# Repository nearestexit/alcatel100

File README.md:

# alcatel100

Custom keyboard designed to use the GMK keycaps from the [Alcatel-Lucent MMK](https://deskthority.net/viewtopic.php?t=23887).
Designed in Onshape and KiCad.
Powered by [QMK](https://github.com/qmk/qmk_firmware).

## Overview
The Alcatel MMK has a beautiful set of keycaps, but the Enter, Backspace, and Right Shift are 0.25u shorter than normal. They are rarely, if ever, used on customs.
The keycaps were originally made by Cherry, but later GMK took over production.

I designed this for fun. It is not an entry-level keyboard, and it is not intended for a Group Buy.
I'm sharing the production and source files with the goal of serving as a reference for other designers.

## Design Goals
- Box-on-wedge with seamless sides all around, including the back
- Left half of the keyboard isolated from the right half
- Single-color PWM-dimmable backlight
- Uniform 4.8mm bezels

**Case Source (Onshape):** https://cad.onshape.com/documents/5081b96c77523c56bb0f8f6b/w/91dc47074a8fd3b0ca2e25d0/e/6e8ed4262c52380f9f8bfe9b

## PCB
The PCB supports both configurations of split right shift, and also split numpad enter. Unfortunately, after the PCB was manufactured, I discovered that the Cherry version of the keyset has a 6.25u spacebar that only has an offset stem, while the GMK version of the keyset has a 6.25u spacebar that supports both centered and offset stems. The PCB and bottom case only support the centered stem location.
I ordered a single bare PCB from EuroCircuits and hand-soldered the components, so I do not have JLCPCB production files available.

## Bill of Materials

| Item  | Quantity | Link |
| ------------- | ------------- | ------------- | 
| Ribbon Cable | 1 | https://www.digikey.com/en/products/detail/molex/0151660207/3281088 |
| 3M SJ5302 | 4  | https://www.3m.com/3M/en_US/p/d/b5005035183/ |
| Unified Daughterboard  | 1  | https://cannonkeys.com/products/unified-daughterboard-and-jst-cable |
| M2.5x0.45x8mm SHCS | 6  | https://www.mcmaster.com/91292A012/ |
| 10cm Molex to JST Cable | 1 | https://cannonkeys.com/products/unified-daughterboard-and-jst-cable |
| M2.5x0.45x16mm SHCS | 1 | https://www.mcmaster.com/91292A018/ |
| M2.5x0.45x20mm SHCS | 6 | https://www.mcmaster.com/91292A019/ |
| M2x0.4x4mm SHCS | 10 | https://www.mcmaster.com/91292A005/ |
| M3x0.5x6mm Countersunk Screw | 5 | https://www.mcmaster.com/92125A126/ |
| M3x0.5x8mm Countersunk Screw | 8 | https://www.mcmaster.com/92125A128/ |

## Backlight

Each lock light is controlled by a separate pin and has a fixed brightness. The remainder of the windowed keys are all on the same PWM dimmable circuit.
I used [these LEDs](https://www.digikey.com/en/products/detail/american-bright-optoelectronics-corporation/BL-B8141-TRS20A/22486924), which have a nice color, but MX LEDs are actually supposed to be 3mm *flangeless* LEDs. These LEDs are *flanged* 3mm. I had to clip off all the flanges (not fun).

## Firmware

A QMK .bin file is provided for flashing, as well as QMK source files. I can port it to Vial upon request.

## Credits

Everyone in the Keyboard Atelier who has helped me over the past 2 years.

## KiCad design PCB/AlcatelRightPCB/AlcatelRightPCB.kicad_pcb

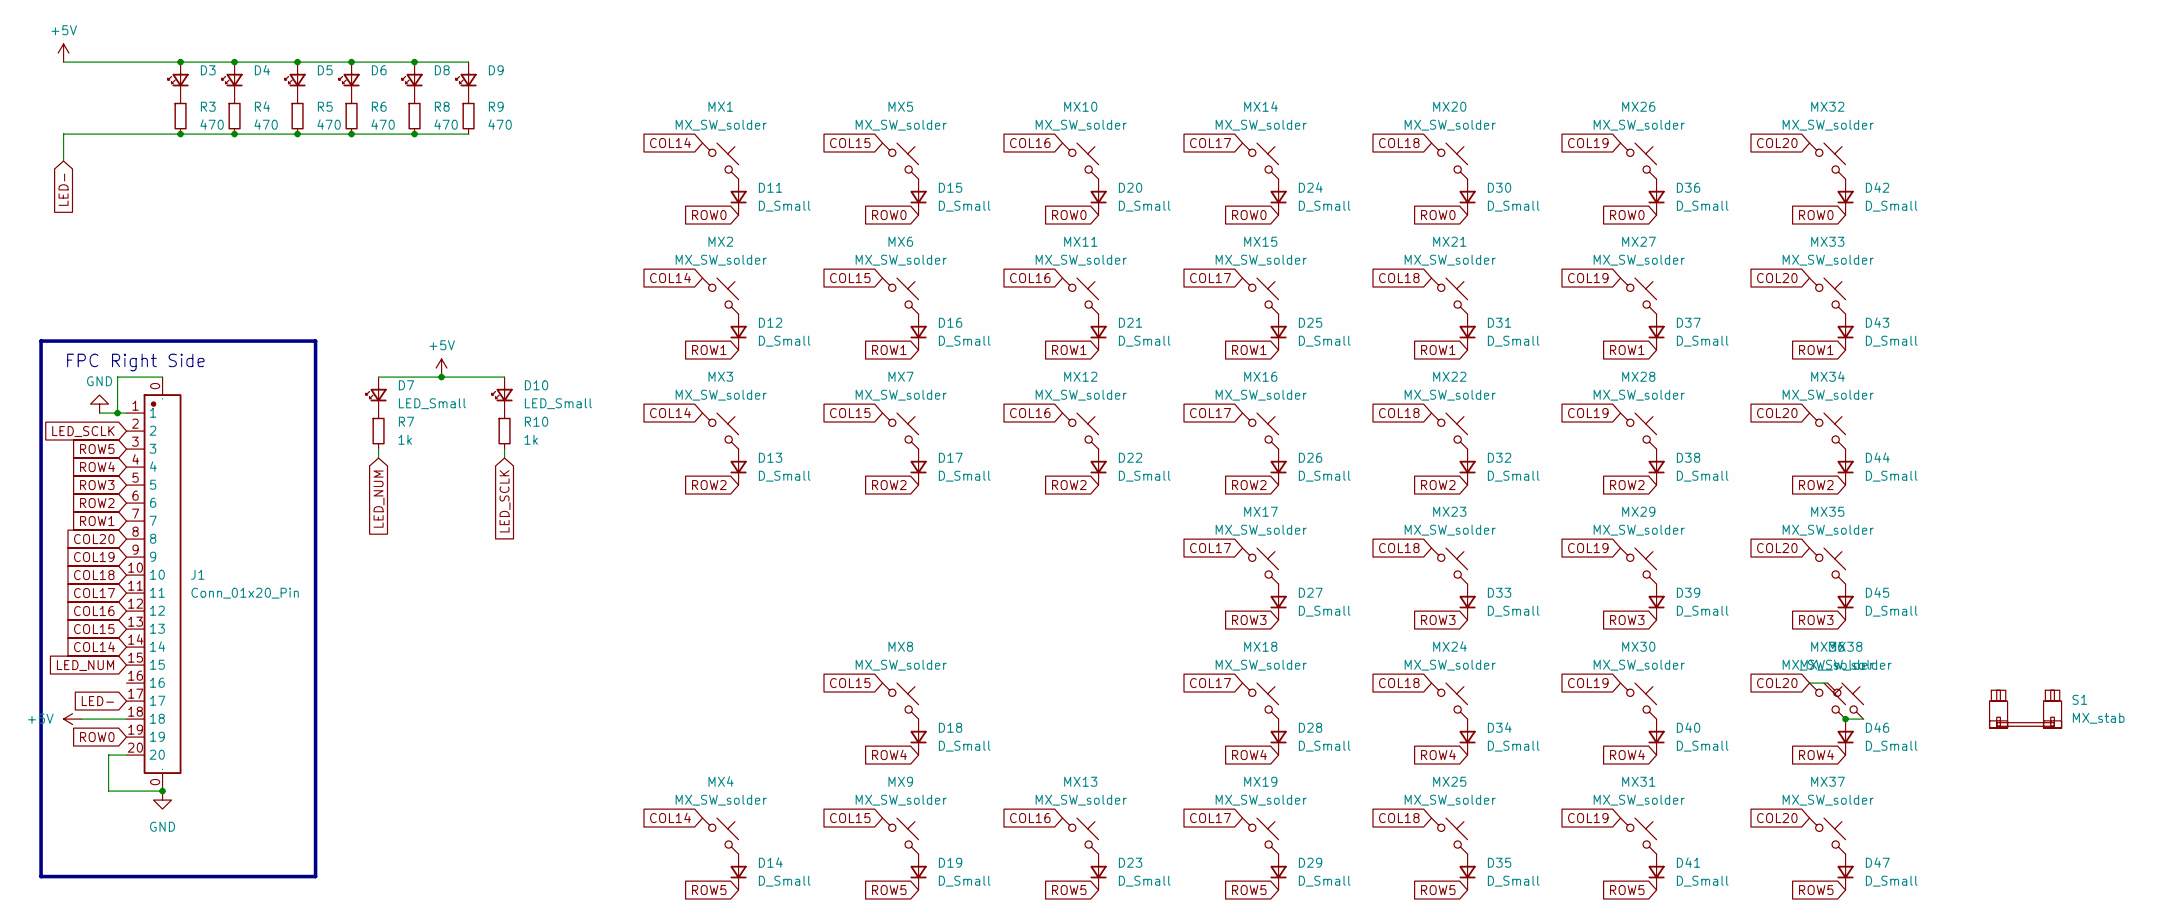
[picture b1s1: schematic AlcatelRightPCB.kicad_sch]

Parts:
D3, D4, D5, D6, D8, D9: LED_MX_3mm_Offset
D7, D10: LED_Small; LED_MX_3mm_Offset
D11, D12, D13, D14, D15, D16, D17, D18, D19, D20, D21, D22, D23, D24, D25, D26, D27, D28, D29, D30, D31, D32, D33, D34, D35, D36, D37, D38, D39, D40, D41, D42, D43, D44, D45, D46, D47: D_Small; D_SOD-123_ShiftedSilkscreen
J1: Conn_01x20_Pin; CONN-SMD_20P-P0.50_10051922-2010ELF
MX1, MX2, MX3, MX4, MX5, MX6, MX7, MX8, MX9, MX10, MX11, MX12, MX13, MX14, MX15, MX16, MX17, MX18, MX19, MX20, MX21, MX22, MX23, MX24, MX25, MX26, MX27, MX28, MX29, MX30, MX31, MX32, MX33, MX34, MX35, MX36, MX37: MX_SW_solder; SW_MX_1u
MX38: MX_SW_solder; SW_MX_HS_CPG151101S11_No_PTH_Edge
R3, R4, R5, R6, R8, R9: 470; R_0805_2012Metric
R7, R10: 1k; R_0805_2012Metric
S1: MX_stab; STAB_MX_2u

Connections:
+5V: D3.2 (A), D4.2 (A), D5.2 (A), D6.2 (A), D7.2 (A), D8.2 (A), D9.2 (A), D10.2 (A), J1.18
COL14: J1.14, MX1.1, MX2.1, MX3.1, MX4.1
COL15: J1.13, MX5.1, MX6.1, MX7.1, MX8.1, MX9.1
COL16: J1.12, MX10.1, MX11.1, MX12.1, MX13.1
COL17: J1.11, MX14.1, MX15.1, MX16.1, MX17.1, MX18.1, MX19.1
COL18: J1.10, MX20.1, MX21.1, MX22.1, MX23.1, MX24.1, MX25.1
COL19: J1.9, MX26.1, MX27.1, MX28.1, MX29.1, MX30.1, MX31.1
COL20: J1.8, MX32.1, MX33.1, MX34.1, MX35.1, MX36.1, MX37.1, MX38.1
GND: J1.0, J1.1, J1.20
LED-: J1.17, R3.2, R4.2, R5.2, R6.2, R8.2, R9.2
LED_NUM: J1.15, R7.2
LED_SCLK: J1.2, R10.2
unnamed: D3.1 (K), R3.1
unnamed: D4.1 (K), R4.1
unnamed: D5.1 (K), R5.1
unnamed: D6.1 (K), R6.1
unnamed: D7.1 (K), R7.1
unnamed: D8.1 (K), R8.1
unnamed: D9.1 (K), R9.1
unnamed: D10.1 (K), R10.1
unnamed: D11.2 (A), MX1.2
unnamed: D12.2 (A), MX2.2
unnamed: D13.2 (A), MX3.2
unnamed: D14.2 (A), MX4.2
unnamed: D15.2 (A), MX5.2
unnamed: D16.2 (A), MX6.2
unnamed: D17.2 (A), MX7.2
unnamed: D18.2 (A), MX8.2
unnamed: D19.2 (A), MX9.2
unnamed: D20.2 (A), MX10.2
unnamed: D21.2 (A), MX11.2
unnamed: D22.2 (A), MX12.2
unnamed: D23.2 (A), MX13.2
unnamed: D24.2 (A), MX14.2
unnamed: D25.2 (A), MX15.2
unnamed: D26.2 (A), MX16.2
unnamed: D27.2 (A), MX17.2
unnamed: D28.2 (A), MX18.2
unnamed: D29.2 (A), MX19.2
unnamed: D30.2 (A), MX20.2
unnamed: D31.2 (A), MX21.2
unnamed: D32.2 (A), MX22.2
unnamed: D33.2 (A), MX23.2
unnamed: D34.2 (A), MX24.2
unnamed: D35.2 (A), MX25.2
unnamed: D36.2 (A), MX26.2
unnamed: D37.2 (A), MX27.2
unnamed: D38.2 (A), MX28.2
unnamed: D39.2 (A), MX29.2
unnamed: D40.2 (A), MX30.2
unnamed: D41.2 (A), MX31.2
unnamed: D42.2 (A), MX32.2
unnamed: D43.2 (A), MX33.2
unnamed: D44.2 (A), MX34.2
unnamed: D45.2 (A), MX35.2
unnamed: D46.2 (A), MX36.2, MX38.2
unnamed: D47.2 (A), MX37.2
ROW0: D11.1 (K), D15.1 (K), D20.1 (K), D24.1 (K), D30.1 (K), D36.1 (K), D42.1 (K), J1.19
ROW1: D12.1 (K), D16.1 (K), D21.1 (K), D25.1 (K), D31.1 (K), D37.1 (K), D43.1 (K), J1.7
ROW2: D13.1 (K), D17.1 (K), D22.1 (K), D26.1 (K), D32.1 (K), D38.1 (K), D44.1 (K), J1.6
ROW3: D27.1 (K), D33.1 (K), D39.1 (K), D45.1 (K), J1.5
ROW4: D18.1 (K), D28.1 (K), D34.1 (K), D40.1 (K), D46.1 (K), J1.4
ROW5: D14.1 (K), D19.1 (K), D23.1 (K), D29.1 (K), D35.1 (K), D41.1 (K), D47.1 (K), J1.3

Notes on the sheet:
FPC Right Side

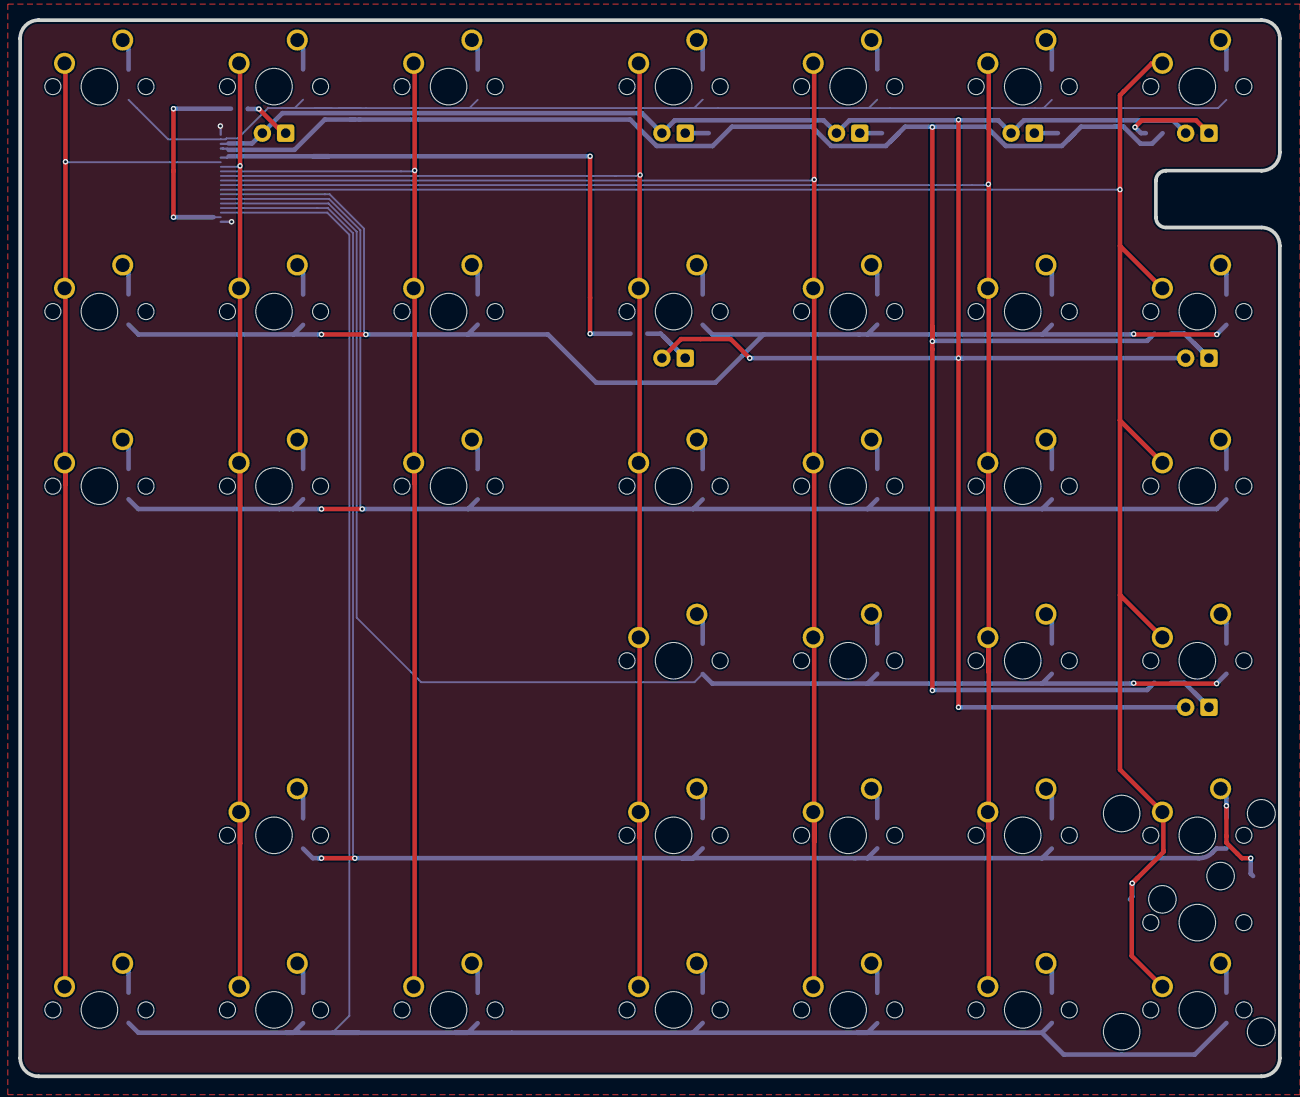
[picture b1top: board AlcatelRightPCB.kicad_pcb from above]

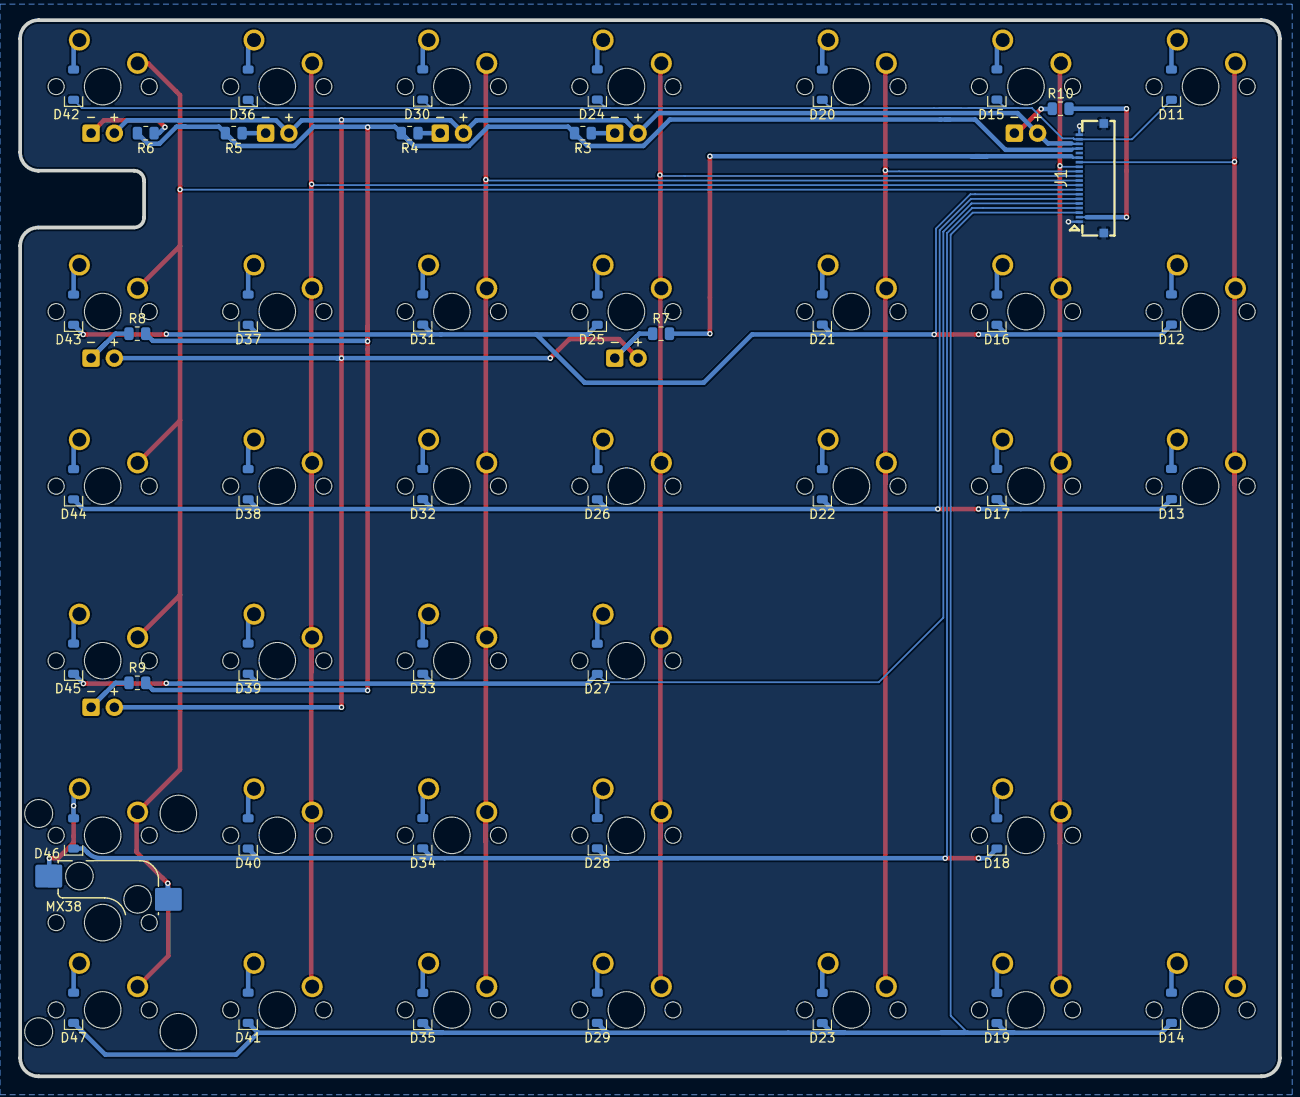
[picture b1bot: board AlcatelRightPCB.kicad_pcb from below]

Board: 2 copper layers, 137.5 x 115.2 mm, 93 parts (47 on the bottom side), 63 nets.

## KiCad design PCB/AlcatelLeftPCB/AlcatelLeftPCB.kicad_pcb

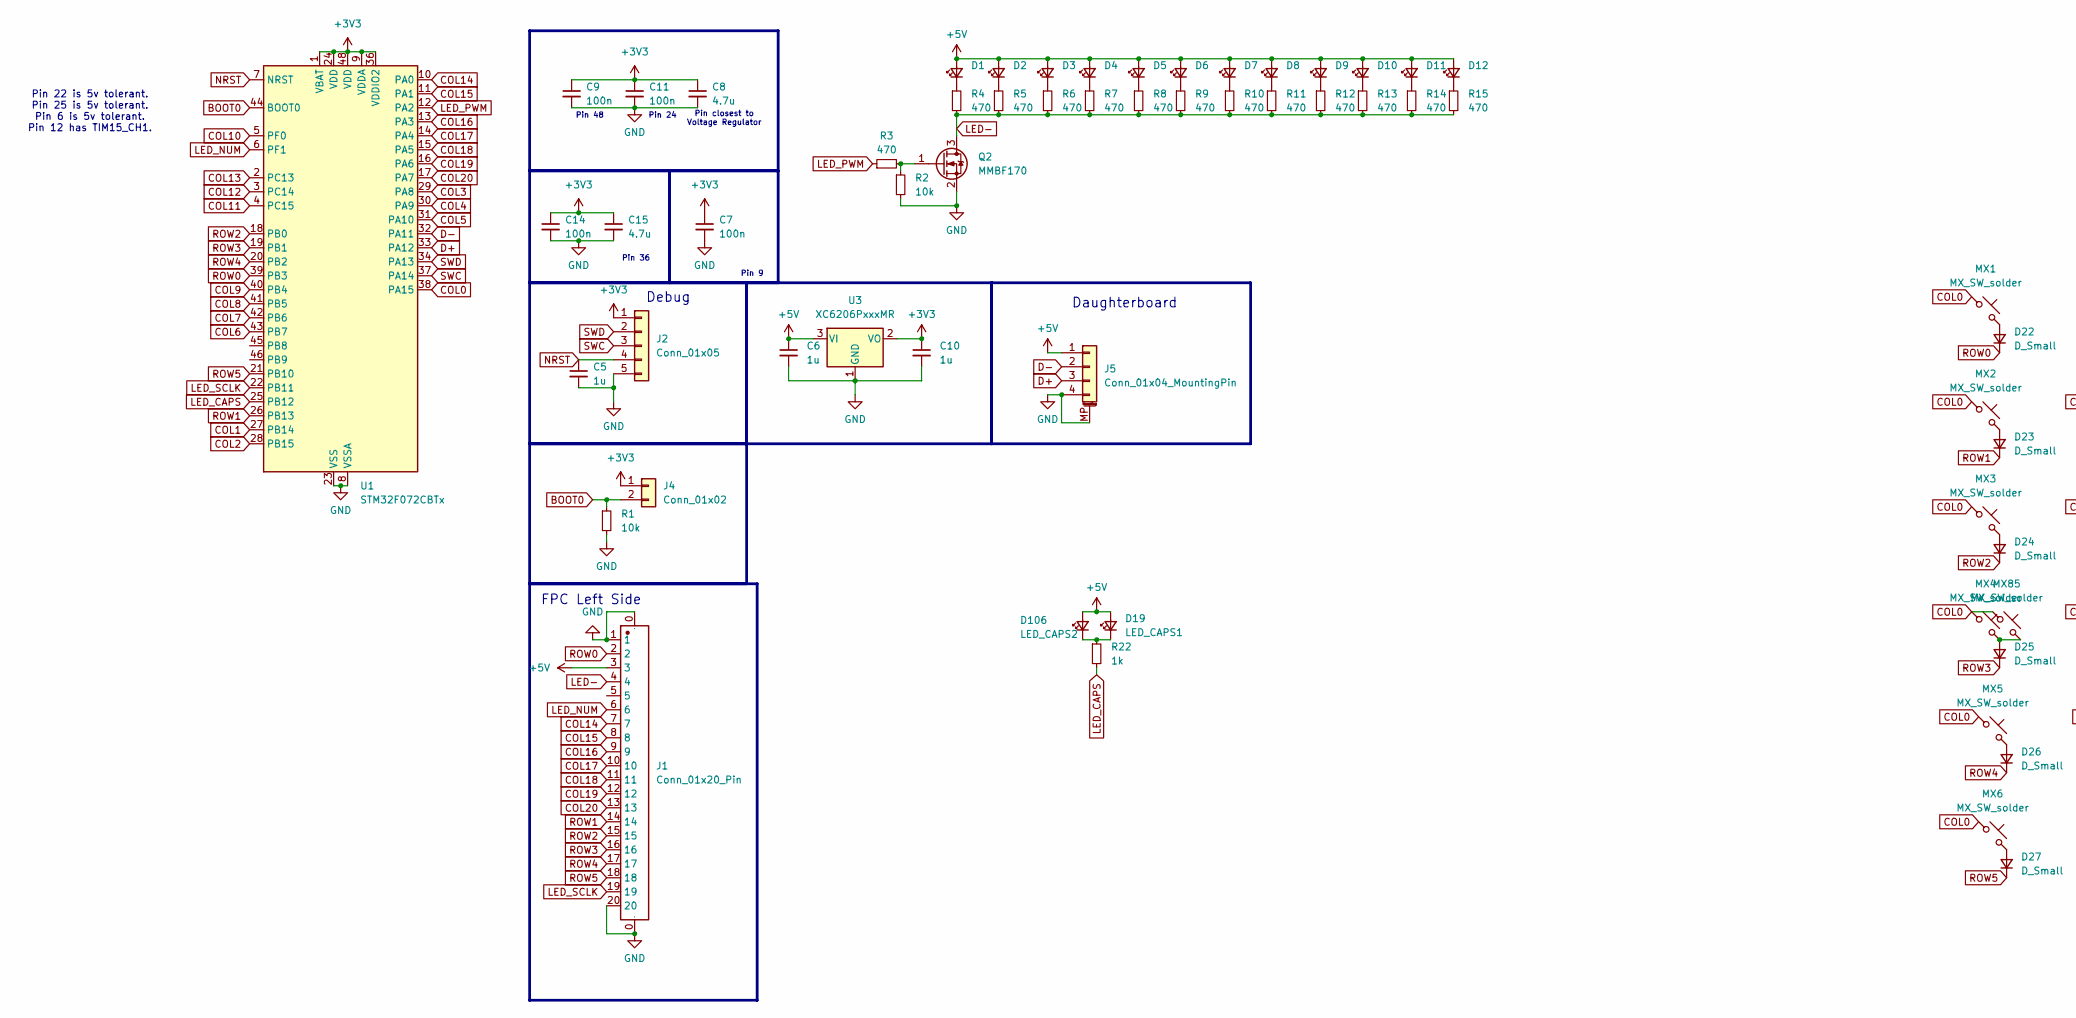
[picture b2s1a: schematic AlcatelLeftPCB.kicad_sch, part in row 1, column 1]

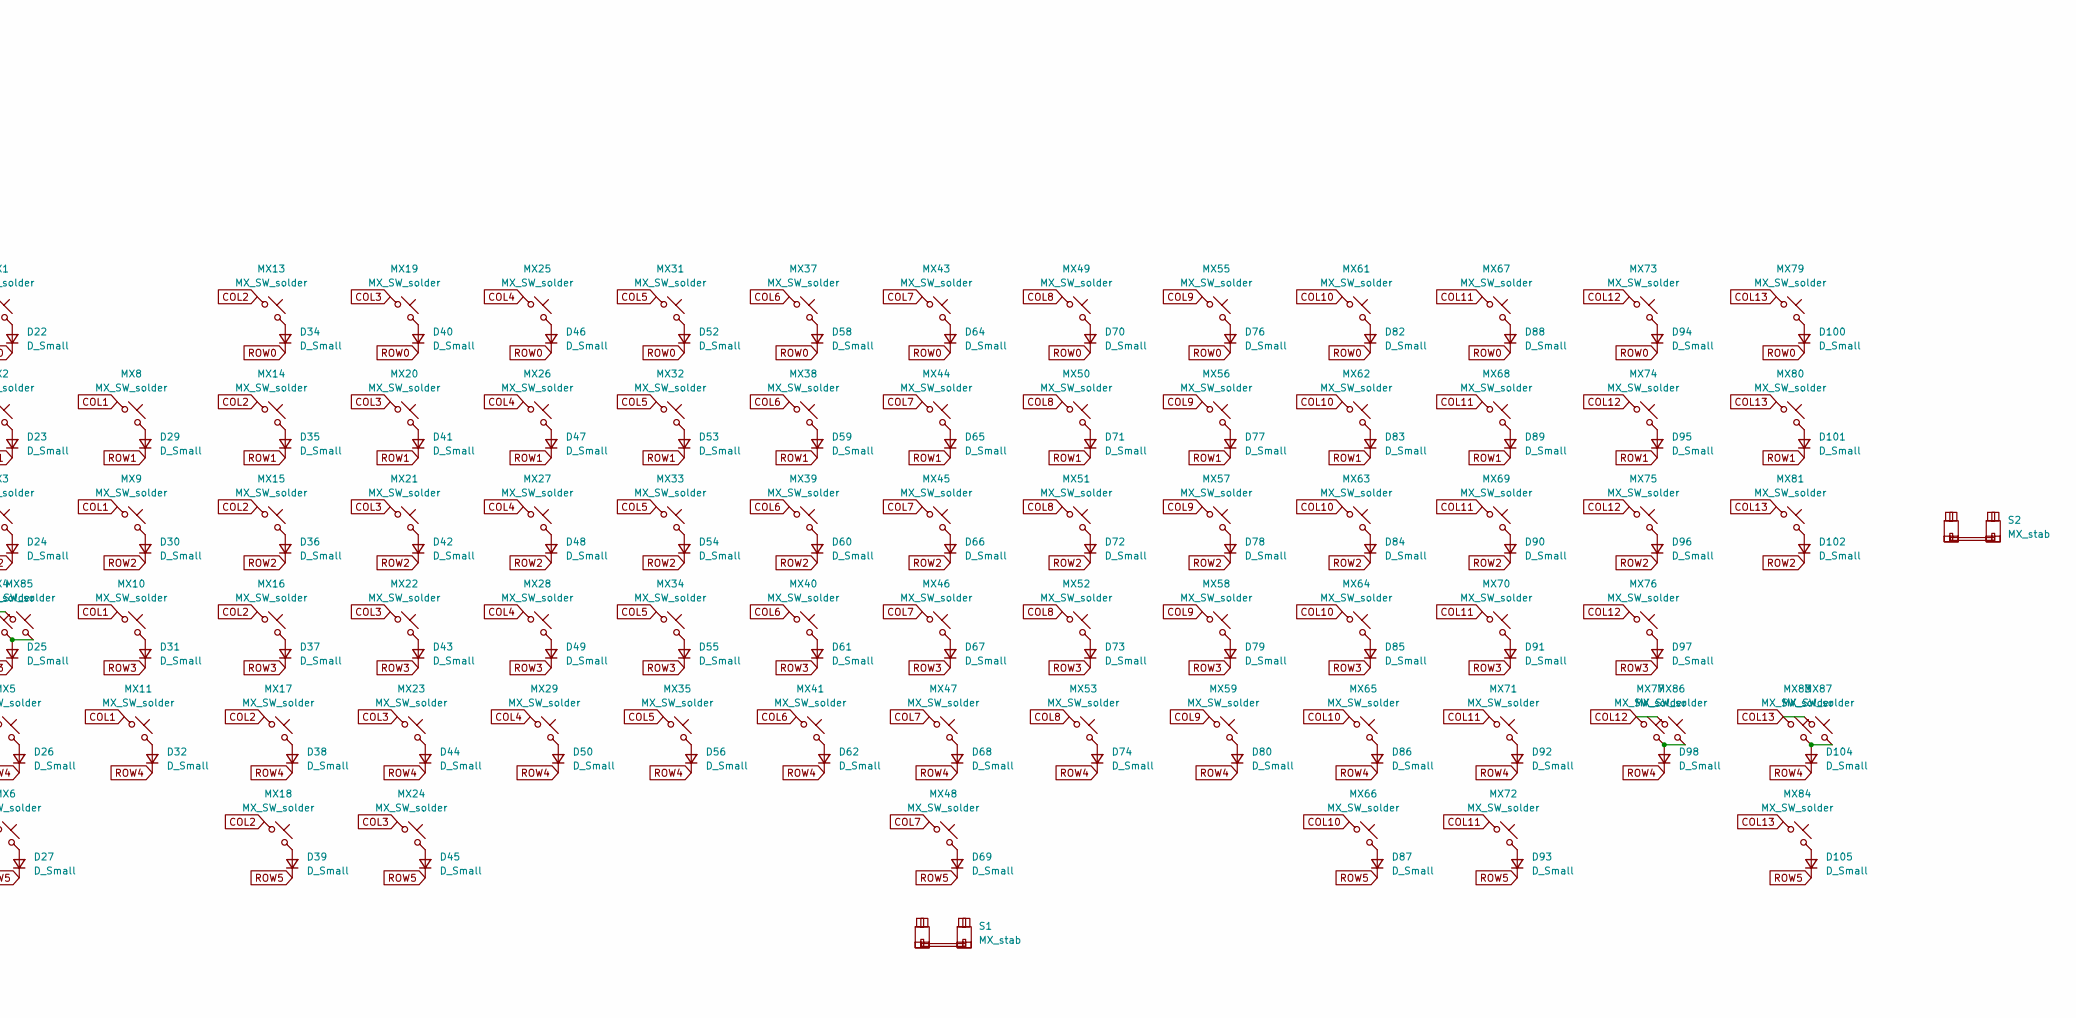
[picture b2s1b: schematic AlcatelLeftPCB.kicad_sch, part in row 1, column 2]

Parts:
C5, C6, C10: 1u; C_0805_2012Metric
C7, C9, C11, C14: 100n; C_0603_1608Metric
C8, C15: 4.7u; C_0603_1608Metric
D1, D2, D3, D4, D5, D6, D7, D8, D9, D10, D11, D12: LED_MX_3mm_Offset
D19: LED_CAPS1; LED_MX_3mm_Offset_Flipped
D22, D23, D24, D25, D26, D27, D29, D30, D31, D32, D34, D35, D36, D37, D38, D39, D40, D41, D42, D43, D44, D45, D46, D47, D48, D49, D50, D52, D53, D54, D55, D56, D58, D59, D60, D61, D62, D64, D65, D66, D67, D68, D69, D70, D71, D72, D73, D74, D76, D77, D78, D79, D80, D82, D83, D84, D85, D86, D87, D88, D89, D90, D91, D92, D93, D94, D95, D96, D97, D98, D100, D101, D102, D104, D105: D_Small; D_SOD-123_ShiftedSilkscreen
D106: LED_CAPS2; LED_MX_3mm_Offset
J1: Conn_01x20_Pin; CONN-SMD_20P-P0.50_10051922-2010ELF
J2: Conn_01x05; PinHeader_1x05_P2.54mm_DEBUG
J4: Conn_01x02; PinHeader_1x02_P2.54mm_BOOT
J5: Conn_01x04_MountingPin; JST_SH_SM04B-SRSS-TB_1x04-1MP_P1.00mm_Horizontal
MX1, MX2, MX3, MX4, MX5, MX6, MX8, MX9, MX10, MX11, MX13, MX14, MX15, MX16, MX17, MX18, MX19, MX20, MX21, MX22, MX23, MX24, MX25, MX26, MX27, MX28, MX29, MX31, MX32, MX33, MX34, MX35, MX37, MX38, MX39, MX40, MX41, MX43, MX44, MX45, MX46, MX47, MX49, MX50, MX51, MX52, MX53, MX55, MX56, MX57, MX58, MX59, MX61, MX62, MX63, MX64, MX65, MX66, MX67, MX68, MX69, MX70, MX71, MX72, MX73, MX74, MX75, MX76, MX77, MX79, MX80, MX83, MX84, MX85, MX86, MX87: MX_SW_solder; SW_MX_1u
MX48, MX81: MX_SW_solder; SW_MX_HS_CPG151101S11_0.125ring
Q2: MMBF170; SOT-23
R1, R2: 10k; R_0805_2012Metric
R3, R4, R5, R6, R7, R8, R9, R10, R11, R12, R13, R14, R15: 470; R_0805_2012Metric
R22: 1k; R_0805_2012Metric
S1: MX_stab; STAB_MX_6.25u
S2: MX_stab; STAB_MX_2u
U1: STM32F072CBTx; LQFP-48_7x7mm_P0.5mm
U3: XC6206PxxxMR; SOT-23-3

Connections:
+3V3: C7.1, C8.1, C9.1, C10.1, C11.1, C14.1, C15.1, J2.1, J4.1, U1.1 (VBAT), U1.9 (VDDA), U1.24 (VDD), U1.36 (VDDIO2), U1.48 (VDD), U3.2 (VO)
+5V: C6.1, D1.2 (A), D2.2 (A), D3.2 (A), D4.2 (A), D5.2 (A), D6.2 (A), D7.2 (A), D8.2 (A), D9.2 (A), D10.2 (A), D11.2 (A), D12.2 (A), D19.2 (A), D106.2 (A), J1.3, J5.1, U3.3 (VI)
BOOT0: J4.2, R1.1, U1.44 (BOOT0)
COL0: MX1.1, MX2.1, MX3.1, MX4.1, MX5.1, MX6.1, MX85.1, U1.38 (PA15)
COL1: MX8.1, MX9.1, MX10.1, MX11.1, U1.27 (PB14)
COL2: MX13.1, MX14.1, MX15.1, MX16.1, MX17.1, MX18.1, U1.28 (PB15)
COL3: MX19.1, MX20.1, MX21.1, MX22.1, MX23.1, MX24.1, U1.29 (PA8)
COL4: MX25.1, MX26.1, MX27.1, MX28.1, MX29.1, U1.30 (PA9)
COL5: MX31.1, MX32.1, MX33.1, MX34.1, MX35.1, U1.31 (PA10)
COL6: MX37.1, MX38.1, MX39.1, MX40.1, MX41.1, U1.43 (PB7)
COL7: MX43.1, MX44.1, MX45.1, MX46.1, MX47.1, MX48.1, U1.42 (PB6)
COL8: MX49.1, MX50.1, MX51.1, MX52.1, MX53.1, U1.41 (PB5)
COL9: MX55.1, MX56.1, MX57.1, MX58.1, MX59.1, U1.40 (PB4)
COL10: MX61.1, MX62.1, MX63.1, MX64.1, MX65.1, MX66.1, U1.5 (PF0)
COL11: MX67.1, MX68.1, MX69.1, MX70.1, MX71.1, MX72.1, U1.4 (PC15)
COL12: MX73.1, MX74.1, MX75.1, MX76.1, MX77.1, MX86.1, U1.3 (PC14)
COL13: MX79.1, MX80.1, MX81.1, MX83.1, MX84.1, MX87.1, U1.2 (PC13)
COL14: J1.7, U1.10 (PA0)
COL15: J1.8, U1.11 (PA1)
COL16: J1.9, U1.13 (PA3)
COL17: J1.10, U1.14 (PA4)
COL18: J1.11, U1.15 (PA5)
COL19: J1.12, U1.16 (PA6)
COL20: J1.13, U1.17 (PA7)
D+: J5.3, U1.33 (PA12)
D-: J5.2, U1.32 (PA11)
GND: C5.2, C6.2, C7.2, C8.2, C9.2, C10.2, C11.2, C14.2, C15.2, J1.0, J1.1, J1.20, J2.5, J5.4, J5.MP (MountPin), Q2.2 (S), R1.2, R2.2, U1.8 (VSSA), U1.23 (VSS), U1.35 (VSS), U1.47 (VSS), U3.1 (GND)
LED-: J1.4, Q2.3 (D), R4.2, R5.2, R6.2, R7.2, R8.2, R9.2, R10.2, R11.2, R12.2, R13.2, R14.2, R15.2
LED_CAPS: R22.2, U1.25 (PB12)
LED_NUM: J1.6, U1.6 (PF1)
LED_PWM: R3.1, U1.12 (PA2)
LED_SCLK: J1.19, U1.22 (PB11)
NRST: C5.1, J2.4, U1.7 (NRST)
unnamed: D1.1 (K), R4.1
unnamed: D2.1 (K), R5.1
unnamed: D3.1 (K), R6.1
unnamed: D4.1 (K), R7.1
unnamed: D5.1 (K), R8.1
unnamed: D6.1 (K), R9.1
unnamed: D7.1 (K), R10.1
unnamed: D8.1 (K), R11.1
unnamed: D9.1 (K), R12.1
unnamed: D10.1 (K), R13.1
unnamed: D11.1 (K), R14.1
unnamed: D12.1 (K), R15.1
unnamed: D22.2 (A), MX1.2
unnamed: D23.2 (A), MX2.2
unnamed: D24.2 (A), MX3.2
unnamed: D25.2 (A), MX4.2, MX85.2
unnamed: D26.2 (A), MX5.2
unnamed: D27.2 (A), MX6.2
unnamed: D29.2 (A), MX8.2
unnamed: D30.2 (A), MX9.2
unnamed: D31.2 (A), MX10.2
unnamed: D32.2 (A), MX11.2
unnamed: D34.2 (A), MX13.2
unnamed: D35.2 (A), MX14.2
unnamed: D36.2 (A), MX15.2
unnamed: D37.2 (A), MX16.2
unnamed: D38.2 (A), MX17.2
unnamed: D39.2 (A), MX18.2
unnamed: D40.2 (A), MX19.2
unnamed: D41.2 (A), MX20.2
unnamed: D42.2 (A), MX21.2
unnamed: D43.2 (A), MX22.2
unnamed: D44.2 (A), MX23.2
unnamed: D45.2 (A), MX24.2
unnamed: D46.2 (A), MX25.2
unnamed: D47.2 (A), MX26.2
unnamed: D48.2 (A), MX27.2
unnamed: D49.2 (A), MX28.2
unnamed: D50.2 (A), MX29.2
unnamed: D52.2 (A), MX31.2
unnamed: D53.2 (A), MX32.2
unnamed: D54.2 (A), MX33.2
unnamed: D55.2 (A), MX34.2
unnamed: D56.2 (A), MX35.2
unnamed: D58.2 (A), MX37.2
unnamed: D59.2 (A), MX38.2
unnamed: D60.2 (A), MX39.2
unnamed: D61.2 (A), MX40.2
unnamed: D62.2 (A), MX41.2
unnamed: D64.2 (A), MX43.2
unnamed: D65.2 (A), MX44.2
unnamed: D66.2 (A), MX45.2
unnamed: D67.2 (A), MX46.2
unnamed: D68.2 (A), MX47.2
unnamed: D69.2 (A), MX48.2
unnamed: D70.2 (A), MX49.2
unnamed: D71.2 (A), MX50.2
unnamed: D72.2 (A), MX51.2
unnamed: D73.2 (A), MX52.2
unnamed: D74.2 (A), MX53.2
unnamed: D76.2 (A), MX55.2
unnamed: D77.2 (A), MX56.2
unnamed: D78.2 (A), MX57.2
unnamed: D79.2 (A), MX58.2
unnamed: D80.2 (A), MX59.2
unnamed: D82.2 (A), MX61.2
unnamed: D83.2 (A), MX62.2
unnamed: D84.2 (A), MX63.2
unnamed: D85.2 (A), MX64.2
unnamed: D86.2 (A), MX65.2
unnamed: D87.2 (A), MX66.2
unnamed: D88.2 (A), MX67.2
unnamed: D89.2 (A), MX68.2
unnamed: D90.2 (A), MX69.2
unnamed: D91.2 (A), MX70.2
unnamed: D92.2 (A), MX71.2
unnamed: D93.2 (A), MX72.2
unnamed: D94.2 (A), MX73.2
unnamed: D95.2 (A), MX74.2
unnamed: D96.2 (A), MX75.2
unnamed: D97.2 (A), MX76.2
unnamed: D98.2 (A), MX77.2, MX86.2
unnamed: D100.2 (A), MX79.2
unnamed: D101.2 (A), MX80.2
unnamed: D102.2 (A), MX81.2
unnamed: D104.2 (A), MX83.2, MX87.2
unnamed: D105.2 (A), MX84.2
unnamed: D19.1 (K), D106.1 (K), R22.1
unnamed: Q2.1 (G), R2.1, R3.2
ROW0: D22.1 (K), D34.1 (K), D40.1 (K), D46.1 (K), D52.1 (K), D58.1 (K), D64.1 (K), D70.1 (K), D76.1 (K), D82.1 (K), D88.1 (K), D94.1 (K), D100.1 (K), J1.2, U1.39 (PB3)
ROW1: D23.1 (K), D29.1 (K), D35.1 (K), D41.1 (K), D47.1 (K), D53.1 (K), D59.1 (K), D65.1 (K), D71.1 (K), D77.1 (K), D83.1 (K), D89.1 (K), D95.1 (K), D101.1 (K), J1.14, U1.26 (PB13)
ROW2: D24.1 (K), D30.1 (K), D36.1 (K), D42.1 (K), D48.1 (K), D54.1 (K), D60.1 (K), D66.1 (K), D72.1 (K), D78.1 (K), D84.1 (K), D90.1 (K), D96.1 (K), D102.1 (K), J1.15, U1.18 (PB0)
ROW3: D25.1 (K), D31.1 (K), D37.1 (K), D43.1 (K), D49.1 (K), D55.1 (K), D61.1 (K), D67.1 (K), D73.1 (K), D79.1 (K), D85.1 (K), D91.1 (K), D97.1 (K), J1.16, U1.19 (PB1)
ROW4: D26.1 (K), D32.1 (K), D38.1 (K), D44.1 (K), D50.1 (K), D56.1 (K), D62.1 (K), D68.1 (K), D74.1 (K), D80.1 (K), D86.1 (K), D92.1 (K), D98.1 (K), D104.1 (K), J1.17, U1.20 (PB2)
ROW5: D27.1 (K), D39.1 (K), D45.1 (K), D69.1 (K), D87.1 (K), D93.1 (K), D105.1 (K), J1.18, U1.21 (PB10)
SWC: J2.3, U1.37 (PA14)
SWD: J2.2, U1.34 (PA13)

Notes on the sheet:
Daughterboard
Pin 22 is 5v tolerant. Pin 25 is 5v tolerant. Pin 6 is 5v tolerant. Pin 12 has TIM15_CH1.
Debug
Pin closest to Voltage Regulator
Pin 24
Pin 9
Pin 36
Pin 48
FPC Left Side

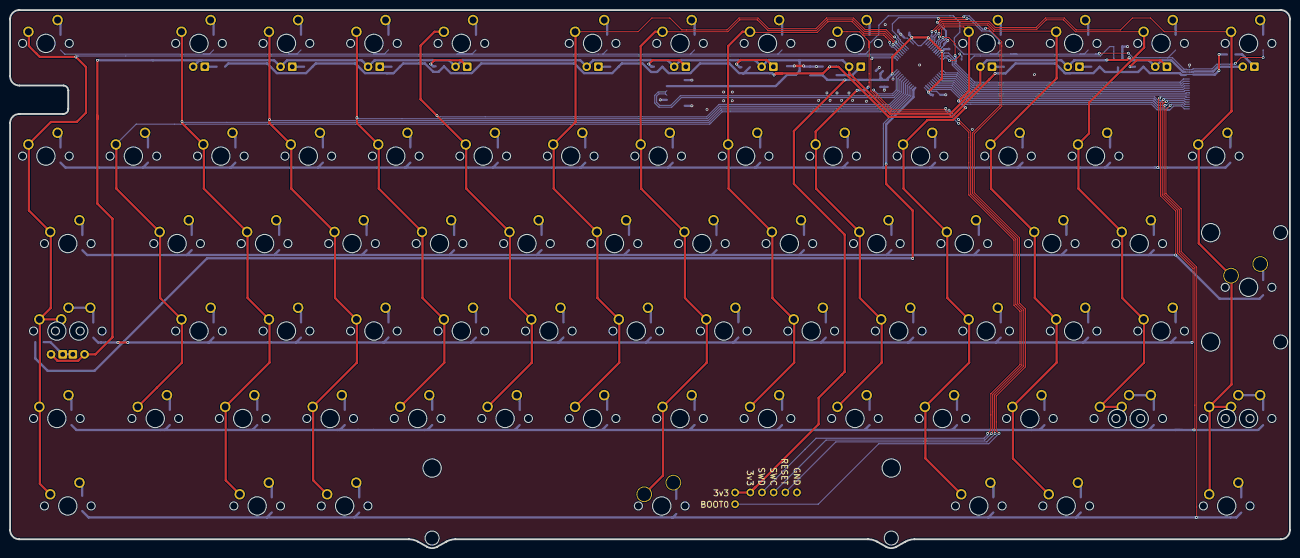
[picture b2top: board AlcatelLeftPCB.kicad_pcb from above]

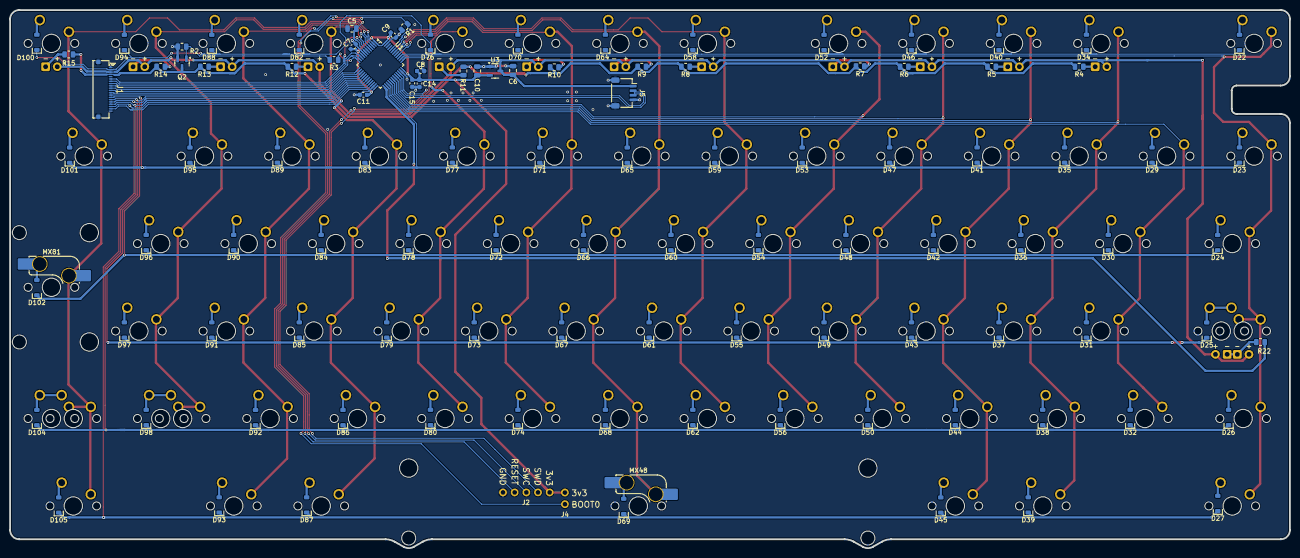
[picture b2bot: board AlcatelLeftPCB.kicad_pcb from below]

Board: 2 copper layers, 278.7 x 117.2 mm, 201 parts (110 on the bottom side), 130 nets.

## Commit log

2025-07-21 Add firmware
